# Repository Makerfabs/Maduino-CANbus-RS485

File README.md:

# Maduino Zero CANBUS
## Introduce

CAN-BUS is a common industrial communication bus because of its long travel distance, medium communication speed, and high reliability, it is the backbone of many protocols with applications in automation, industrial systems, building management. This Maduino Zero CAN-BUS based on SAMD21G18A, with the CAN controller MCP2515 and CAN transceiver MAX3051, to create a ready-to-use CAN-bus port. With this board, you can easily get/send your local data remotely with a standard CAN Bus. For example, you can collect local sensor data, using the Maduino zero ports, and send all the data to remote servers, to create remote-monitor with reliable CAN-Bus communication.<br>
[Makerfabs Wiki](https://www.makerfabs.com/wiki/index.php?title=Maduino_Zero_Canbus_with_RS485) <br>
<br/>

## Features

* ATMEL SAMD21G18A: 32-bit ARM® Cortex®-M0, Arduino Zero bootloader pre-loaded.<br>
* CAN-BUS/ RS-485.<br>
* Implements CAN V2.0 at 1M/s.<br>
* MCP2515 CAN Bus controller and MAX3051 CAN Bus transceiver.<br>
* Allows for Transmission Speeds Up to 16Mbps of RS-485.<br>
* Industrial standard 9 pins sub-D connector.<br>

## Usage

### Software setup

* After installed Arduino, there is no package to support the board (Arduino zero) that is needed to be installed.<br>
* select tools ->Board -> Board Manager, search "Arduino zero" and install "Arduino SAMD Boards".<br>
* Select Tools ->Board -> Arduino Zero (Native USB Port), select Tools -> Port -> com…<br>

### Test

* The sensors or devices which can carry on RS485 or CANbus are connected to the board through cables. in this project, use the same board instead of the device being tested, and connected two board by cables or Dupont Lines to check the communication between boards.<br>
* The pins connection is:<br>

|Maduino Zero CANbus with RS485 |Devices or sensors |
|---|---|
|GND |GND |
|RS485_A |RS485_A |
|RS485_B |RS485_B |
|CAN_H | CAN_H |
|CAN_L | CAN_L |

#### CANBUS
* One board upload the [CAN_Sender.ino](https://github.com/Makerfabs/Maduino-CANbus-RS485/blob/main/CAN_Sender/CAN_Sender.ino) , and the other upload the [CAN_Receiver.ino](https://github.com/Makerfabs/Maduino-CANbus-RS485/blob/main/CAN_Receiver/CAN_Receiver.ino). Both programs include the functions which can realize receiving and sending data in RS485 communication mode and CANBUS communication mode.<br>
* After the upload is successful, open the Serial Monitor and you can observe that the board is receiving and sending data cyclically through CANBUS. The green indicator light on the board will flash when data is received.<br>

<br/>

#### RS485
* Two boards upload the [RS485.ino](https://github.com/Makerfabs/Maduino-CANbus-RS485/blob/main/RS485/RS485.ino) ,
* After the upload is successful, open the Serial Monitor and send data through the Serial Monitor, and receive the data through RS485 communication on another board. The blue indicator light on the board will flash when data is received.<br>

<br/>
<br/>

#### TEST_DHT11_OLED

This project is about data transmission via CANBUS. Use Maduino Zero CANBUS to collect temperature and humidity data and send it through CANBUS, and use the same module to receive and display the data.

<br/>

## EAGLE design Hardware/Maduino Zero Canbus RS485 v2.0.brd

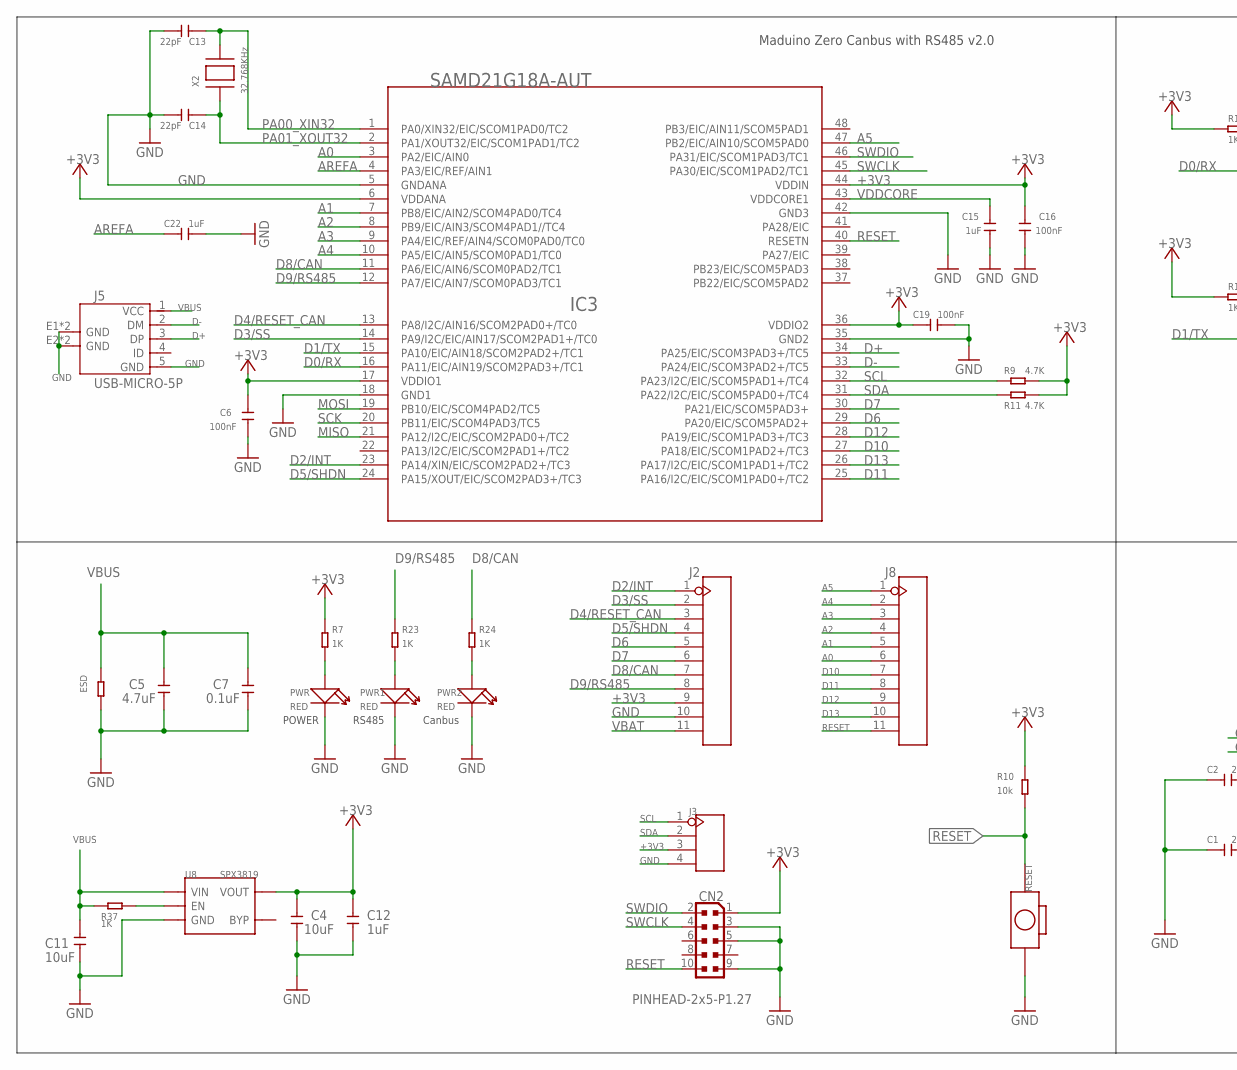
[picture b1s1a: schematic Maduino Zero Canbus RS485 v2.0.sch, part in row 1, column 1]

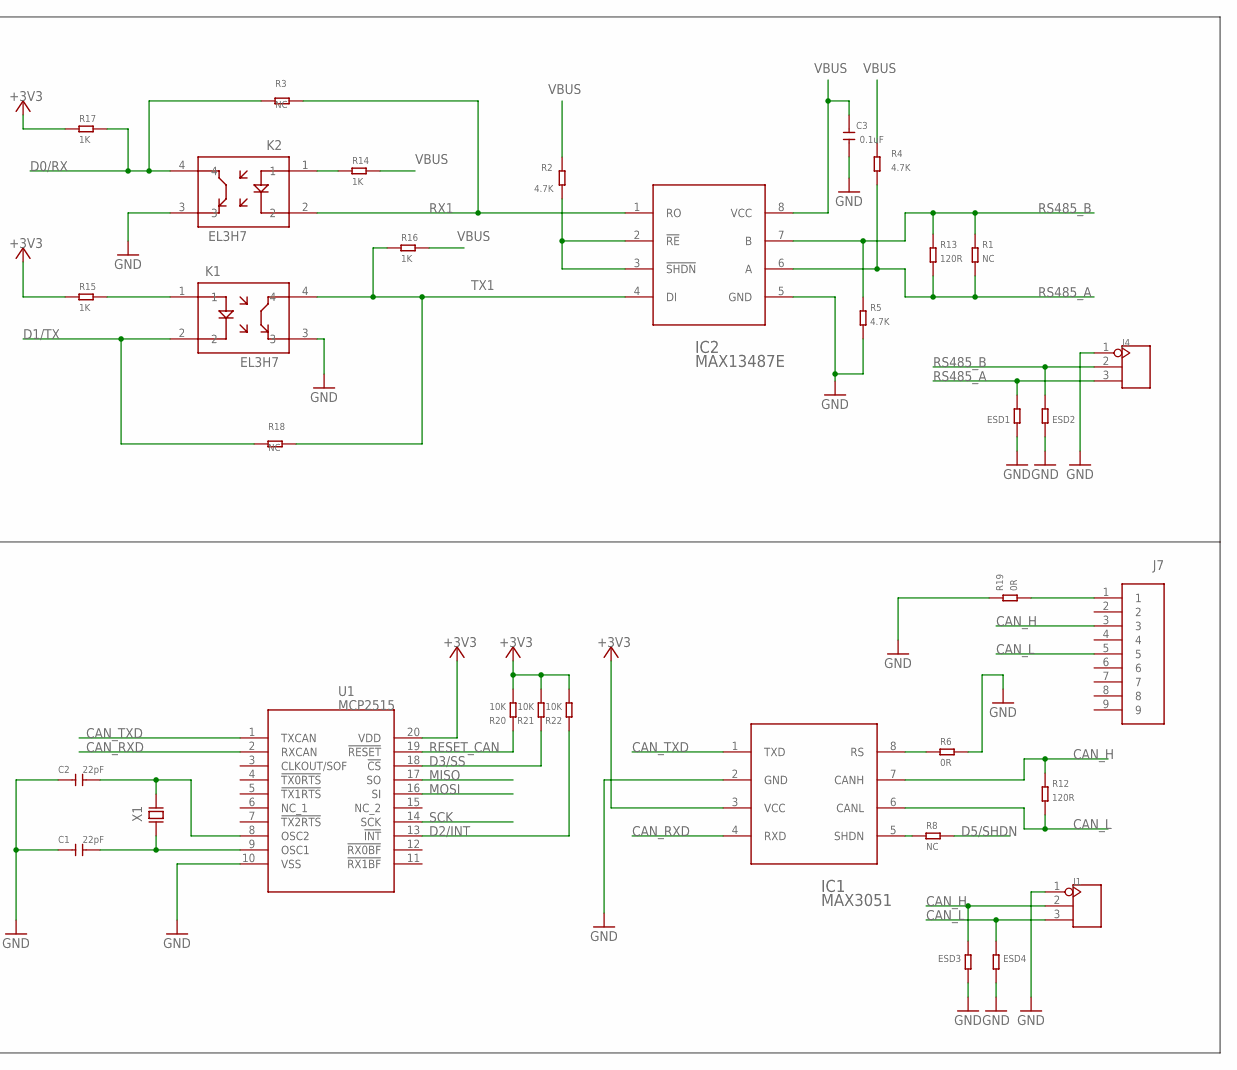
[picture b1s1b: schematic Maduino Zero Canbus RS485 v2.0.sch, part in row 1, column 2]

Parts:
C1, C2, C13, C14: 22pF; 0603
C3, C7: 0.1uF; 0603
C4, C11: 10uF; 0603
C5: 4.7uF; 0603
C6, C16, C19: 100nF; 0603
C12, C15, C22: 1uF; 0603
CN2: PINHEAD-2x5-P1.27; PINHEAD_2X05_127
ESD, ESD1, ESD2: R-0603; R0603
ESD3, ESD4: NC; R0603
IC1: MAX3051; DIP8_MX3051
IC2: MAX13487E; DIP8_MAX13487
IC3: SAMD21G18A-AUT; TQFP48-7X7
J1, J4: HEADER-3P-2.54; 3P-2.54
J2, J8: HEADER-11P-2.54; 11P-2.54
J3: HEADER-4P-60/35MILROUND; 4P-65/35ROUND
J5: USB-MICRO-5P; MICRO-USB-5P
J7: DB9-90; DIP9-DB9-P2.77
K1, K2: EL3H7; SOP-4_P1.27
PWR, PWR1, PWR2: RED; LED-0603
R1, R3, R8, R18: NC; R0603
R2, R4, R5, R9, R11: 4.7K; R0603
R6, R19: 0R; R0603
R7, R14, R15, R16, R17, R23, R24, R37: 1K; R0603
R10: 10k; R0603
R12, R13: 120R; R0603
R20, R21, R22: 10K; R0603
RESET: BOTTON-2P-90D; 2P-7.62X3.56-90D
U1: MCP2515; SSOP-20
U8: SPX3819; SOT23-5
X1: XTAL-8MHZ; SMD-5032_2P_8M
X2: 32.768KHz; XTAL3215

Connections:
+3V3: C4.2, C6.2, C12.2, C16.1, C19.1, CN2.1, IC1.3 (VCC), IC3.6 (VDDANA), IC3.17 (VDDIO1), IC3.36 (VDDIO2), IC3.44 (VDDIN), J2.9, J3.3, R7.1, R9.2, R10.2, R11.2, R15.2, R17.2, R20.1, R21.1, R22.1, U1.20 (VDD), U8.5 (VOUT)
A0: IC3.3 (PA2/EIC/AIN0), J8.6
A1: IC3.7 (PB8/EIC/AIN2/SCOM4PAD0/TC4), J8.5
A2: IC3.8 (PB9/EIC/AIN3/SCOM4PAD1//TC4), J8.4
A3: IC3.9 (PA4/EIC/REF/AIN4/SCOM0PAD0/TC0), J8.3
A4: IC3.10 (PA5/EIC/AIN5/SCOM0PAD1/TC0), J8.2
A5: IC3.47 (PB2/EIC/AIN10/SCOM5PAD0), J8.1
AREFA: C22.1, IC3.4 (PA3/EIC/REF/AIN1)
CAN_H: ESD3.1, IC1.7 (CANH), J1.2, J7.3, R12.1
CAN_L: ESD4.1, IC1.6 (CANL), J1.3, J7.5, R12.2
CAN_RXD: IC1.4 (RXD), U1.2 (RXCAN)
CAN_TXD: IC1.1 (TXD), U1.1 (TXCAN)
D0/RX: IC3.16 (PA11/EIC/AIN19/SCOM2PAD3+/TC1), K2.4, R3.2, R17.1
D1/TX: IC3.15 (PA10/EIC/AIN18/SCOM2PAD2+/TC1), K1.2, R18.2
D2/INT: IC3.23 (PA14/XIN/EIC/SCOM2PAD2+/TC3), J2.1, R22.2, U1.13 (!INT)
D3/SS: IC3.14 (PA9/I2C/EIC/AIN17/SCOM2PAD1+/TC0), J2.2, R21.2, U1.18 (!CS)
D4/RESET_CAN: IC3.13 (PA8/I2C/AIN16/SCOM2PAD0+/TC0), J2.3
D5/SHDN: IC3.24 (PA15/XOUT/EIC/SCOM2PAD3+/TC3), J2.4, R8.1
D6: IC3.29 (PA20/EIC/SCOM5PAD2+), J2.5
D7: IC3.30 (PA21/EIC/SCOM5PAD3+), J2.6
D8/CAN: IC3.11 (PA6/EIC/AIN6/SCOM0PAD2/TC1), J2.7, R24.1
D9/RS485: IC3.12 (PA7/EIC/AIN7/SCOM0PAD3/TC1), J2.8, R23.1
D10: IC3.27 (PA18/EIC/SCOM1PAD2+/TC3), J8.7
D11: IC3.25 (PA16/I2C/EIC/SCOM1PAD0+/TC2), J8.8
D12: IC3.28 (PA19/EIC/SCOM1PAD3+/TC3), J8.9
D13: IC3.26 (PA17/I2C/EIC/SCOM1PAD1+/TC2), J8.10
D+: IC3.34 (PA25/EIC/SCOM3PAD3+/TC5), J5.3 (DP)
D-: IC3.33 (PA24/EIC/SCOM3PAD2+/TC5), J5.2 (DM)
GND: C1.1, C2.1, C3.1, C4.1, C5.1, C6.1, C7.1, C11.1, C12.1, C13.2, C14.2, C15.2, C16.2, C19.2, C22.2, CN2.3, CN2.5, CN2.9, ESD.2, ESD1.1, ESD2.1, ESD3.2, ESD4.2, IC1.2 (GND), IC2.5 (GND), IC3.5 (GNDANA), IC3.18 (GND1), IC3.35 (GND2), IC3.42 (GND3), J1.1, J2.10, J3.4, J4.1, J5.5 (GND), J5.E1 (GND), J5.E2 (GND), J5.P1 (GND), J5.P2 (GND), K1.3, K2.3, PWR.-, PWR1.-, PWR2.-, R5.1, R6.1, R19.2, RESET.P$2 (2), U1.10 (VSS), U8.2 (GND)
MISO: IC3.21 (PA12/I2C/EIC/SCOM2PAD0+/TC2), U1.17 (SO)
MOSI: IC3.19 (PB10/EIC/SCOM4PAD2/TC5), U1.16 (SI)
unnamed: K2.1, R14.2
unnamed: PWR.+, R7.2
unnamed: C2.2, U1.8 (OSC2), X1.2
unnamed: C1.2, U1.9 (OSC1), X1.1
unnamed: K1.1, R15.1
unnamed: J7.1, R19.1
unnamed: PWR1.+, R23.2
unnamed: PWR2.+, R24.2
unnamed: IC1.8 (RS), R6.2
unnamed: IC1.5 (SHDN), R8.2
unnamed: R37.2, U8.3 (EN)
unnamed: IC2.2 (!RE), IC2.3 (!SHDN), R2.1
PA00_XIN32: C13.1, IC3.1 (PA0/XIN32/EIC/SCOM1PAD0/TC2), X2.P$2
PA01_XOUT32: C14.1, IC3.2 (PA1/XOUT32/EIC/SCOM1PAD1/TC2), X2.P$1
RESET: CN2.10, IC3.40 (RESETN), J8.11, R10.1, RESET.P$1 (1)
RESET_CAN: R20.2, U1.19 (!RESET)
RS485_A: ESD1.2, IC2.6 (A), J4.3, R1.1, R4.1, R13.1
RS485_B: ESD2.2, IC2.7 (B), J4.2, R1.2, R5.2, R13.2
RX1: IC2.1 (RO), K2.2, R3.1
SCK: IC3.20 (PB11/EIC/SCOM4PAD3/TC5), U1.14 (SCK)
SCL: IC3.32 (PA23/I2C/EIC/SCOM5PAD1+/TC4), J3.1, R9.1
SDA: IC3.31 (PA22/I2C/EIC/SCOM5PAD0+/TC4), J3.2, R11.1
SWCLK: CN2.4, IC3.45 (PA30/EIC/SCOM1PAD2/TC1)
SWDIO: CN2.2, IC3.46 (PA31/EIC/SCOM1PAD3/TC1)
TX1: IC2.4 (DI), K1.4, R16.2, R18.1
VBAT: J2.11
VBUS: C3.2, C5.2, C7.2, C11.2, ESD.1, IC2.8 (VCC), J5.1 (VCC), R2.2, R4.2, R14.1, R16.1, R37.1, U8.1 (VIN)
VDDCORE: C15.1, IC3.43 (VDDCORE1)

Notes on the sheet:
Maduino Zero Canbus with RS485 v2.0
POWER
RS485
Canbus

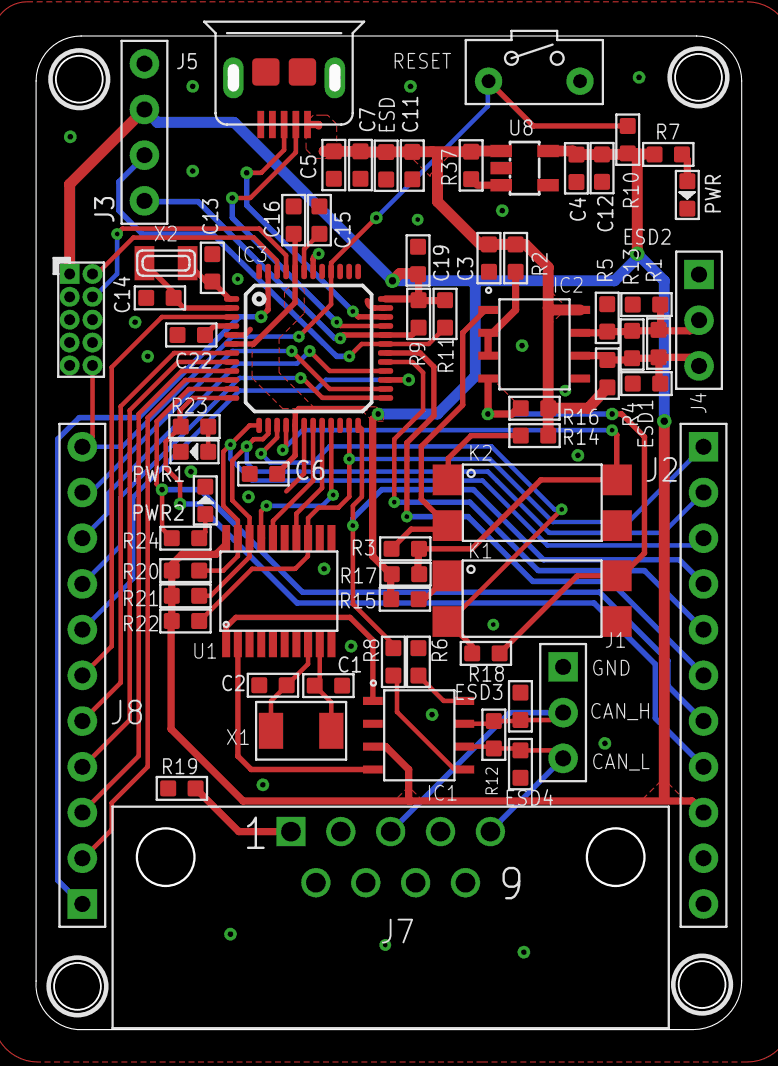
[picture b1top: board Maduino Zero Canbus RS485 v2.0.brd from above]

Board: 2 copper layers, 38.6 x 54.6 mm, 67 parts (1 on the bottom side), 58 nets.

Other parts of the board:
U$1: MAKERFABS_0.3

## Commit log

2020-10-22 add hardware
2020-10-23 updata
2020-10-23 hardware updata
2020-11-10 rename
2020-11-12 create
